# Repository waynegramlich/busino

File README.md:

# Busino

The Busino is an "Arduino-compatible" processor board.

Since just about everybody calls their board "Arduino-compatible",
even when they are not really very compatible, it is prudent to
be more specific.  The Busino uses an Atmel<Sup>&tm;</Sup> AVR
ATmega324P processor.  This processor is in a 40-pin DIP (Dual
In-line Package) and is pretty compatible with the ATmega328
that is used by the ever popular Arudino<Sup>&tm;</Sup> Uno
processor board.  The ATmega324P is used instead of the AtMega324
because it has a second UART (Universal Asynchronous
Receiver/Transmitter) that is reserved for bus communication
between multiple Busino's.  The processor runs at 16MHz just
like the Uno.  The Busino has the same connectors as the Uno
so that most of the Arduino Uno compatible shield can be plugged
into the Busino.  The Busino can be programmed using the
Arduino IDE (Integrated Development Environment.)  Since the
ATmega324P has different package pin assignments, a Busino template
needs to be installed with the IDE to make it work.  Lastly, the
Busino uses a USB to serial cable to program the board instead
of having a dedicated USB to serial conversion chip.  In short,
the Busino is **extremely** compatible with the
Arduino<Sup>&tm;</Sup> system architecture.

There are three other major features of the Busino:

1 There is 10-pin ribbon cable connector that can be used to
  bus multiple Busino's together.  The Busino uses CAN bus
  physical layer transceivers (technically ISO-11898 transceivers)
  over a differential pair for communication.  This is exactly
  the same technology used by automobile manufacturers.  It is
  extremely robust.

  This bus has two power buses -- one for supplying power to
  digital logic (e.g. microprocessors, etc.) and another for
  supplying power to small motors like hobby servos, etc.  The
  separate power buses, reduce noise and cross talk issues.

2 The Busino also has 4 locations to plug in Mini-Shields.
  A mini-shield is very similar in concept to an Arduino
  shield, only smaller.  A mini-shield is 5cm &times; 5cm
  square and has access to all of the power (5V, 3V, Vin)
  and signal pins (D0-D13, A0-A5, RESET, etc.) that are
  accessible to an Arduino shield.  Since there are 4 mini-shield
  locations, up to 4 mini-shields can be plugged into the
  Busino.

3 The Busino is 100% Open Source Hardware and Software.
  The PCB's (Printed Circuit Boards) are designed using
  KiCAD (an open source PCB layout tool.)   The Software
  is released under a GPL software license.  You can 
  make any modifications you want, provided that you
  adhere the very reasonable license requirements.  In
  short, since the Busino team is sharing the stuff with
  you, we want you to share your awesome modifications
  back with us.  If you can make money selling Busino's,
  it is your money, not ours.

## Schematic

The schematic and PCB were developed using the KiCAD
EDA (Engineering Design Automation) software suite.
Like the Busino, KiCAD is also 100% open source with
no arbitrary restrictions.

The schematic described below is for the revision B
of the board.  Each revision is kept in a separate
directory.  Revision B is kept in the `rev_b` directory.
The schematic can be found in `busino.pdf` in the `rev_b`
directory.

The schematic is broken into 7 sheets:

* The top level sheet just shows the common bus that connects
  together all of the common "Arduino" pins between all the
  sheets.  These include D0-D13, A0-A5, #RESET, AREF, and various
  power lines -- VIN, 5V, 3V3, GND, MPWR, and MGND.

* The processor sheet contains most of the *meat* in that
  it shows how the processor is wired up to everything --
  the bus, the voltage regulators, the reset circuitry,
  etc.

* The Arduino shield sheet shows how all of the pins are
  connected to the standard pins that connect to Arudino
  compatible shields.

* The remaining 4 sheets are essentially duplicates of one
  another, where each sheet documents the two connectors
  that connect to a mini-shield.

### Processor Schematic Sheet

Logic power comes in via VIN and is run through
a 5V LDO (Low Drop-Out) LM2940 voltage regulator (U1)
and through another 3.3V LDO LM117T-3.3 volttage
regulator (U3).  It is recommended that at least 6V
be provided to VIN.  C1, C3, and C5 are 22uF tantalum
capacitors to help with regulation.  The .1uF 
capacitor (C8) and .47 Ohm series connection reduces
the ESR (Equivalent Series Resistance) of C3 down
to between 1 and .1 Ohms.  This is required to ensure
that the LM2940 voltage regulator remains stable.
The LM2940 specification sheet can be found in the
`docs` directory.  The 3.3V power output is not
used by the processor; it is only there to provide
3.3V to any Arduino compatible shields that get plugged
into the Busino.   U3 and C5 can be omitted if 3.3V
is not required.

The bus is comes in via 2x5 shrouded header (N8).
MPWR and MGND are directed to the mini-shields to
provide power for motors and such.  LGND and LPWR
supply the logic power.  LPWR is also called VIN
because that is what the Arduino folks called it.

The bus signals come in on CANH and CANL which are
a differential pair that adhere to ISO-11898.  The are
fed into a Microchip MCP2562 CAN bus transceiver (U2).
The TXD and RXD signals are fed to RXD1 and TXD1 on
the processor (U5).  The termination jumper (J1) can
be configured to supply 120 Ohms of termination if
the Busino is at either end of the bus.

The processor is an ATmega324P and comes in 40-pin
DIP (Dual In-line Package).  The goal is to make
the ATmega324P be as compatible as possible with
the standard ATmega328 that is used by the Arduino Uno
product.  Since the ATmega328 comes in a 28-pin DIP
there are some differences in the pin assignments.
These have been carefully thought out.  PB1 and PD4
are connected because the Arduino has both a PWM
output and T1 attached to the same line.  PD4 has
a PWM output and PB1 has T1.  Along similar lines,
PD7 is connected to PB5, PC0 is connected to PA5,
and PC1 is connected to PA4.  The standard Arduino
16MHz crystal (X1) and two 18pF capacitors (C2 and C4)
connected to XTAL1 and XTAL2.

Since it was basically free to do so, an AVR compatible
2x5 shrouded header (N16) is provided for JTAG debugging.
It is expected that only people who really want to do
this, will need the JTAG connector, so they will have
to find the connector and solder it in.

The processor is programmed to have a bootloader installed
in it.  Unlike the Arduino, the Busino does not have a
dedicated USB to serial connection.  Instead it uses
a common USB to serial connector from FTDI.  The FTDI
cable can be either a 5V cable or a 3.3V cable.  In
general the 3.3V cable is preferred.  The FTDI cable
plugs into the 1x6 header (N9).  The RXD and TXD
signals are routed through 1K resistors (R2 and R3) to
the RXD0 and TXD0 pins of the processor (U5).  The 1K
resistor allows an Arduino shield to *override* the
programming that comes in the FTDI cable.

It should be noted that the output of TXD from the processor
is 5V.  The 3.3V FTDI serial cable has 5V tolerant inputs
so no damage occurs.  Also, the TXD output from the FTDI
cable is either 3.3V or 5V.  For the processor #RESET line,
any voltage above .6*Vcc (= .6*5V = .3V) is treated as a
"high".  Both 3.3V and 5V are within specification.

The processor can be reset in any of the following
methods:

* The reset button (SW1) can be depressed.

* The JTAG adapter (N16) can assert #NRST

* The bus can send a "break" character which will cause the
  processor to reset.

* The host computer can assert #RTS on the FTD cable (N9).

The #RTS signal can be either 3.3V or 5V.  This is fed
into U4F which is a 74HCT05 open collector inverter.
The HCT logic family will treat any voltage that exceeds
2V as a logic "high".  The 100K pull-up resistor R4
ensures that the U4F input is pulled high if no FTDI
serial cable is plugged in.  U4F and U4E basically
provide a buffer that converts any 3.3V signals up to 5V.
The 100K resistor R12 is needed because U4F has an open
collector output.

The two 10K resistors (R7, R13) in conjunction with .1uF
capacitor (C6) and Schottky diode (D1) used to generate
a #RESET pulse as follows:

* The #RTS line idles "high".  This cause both ends of C6
  to be pulled up to 5V, thereby fully discharging C6 so
  that there is 0V across it.

* At the beginning of programming, #RTS is asserted low by
  the programming software for the duration of programming.
  When #RTS is asserted low, the output of U4E goes low.
  Since there is 0V across C6, the #RESET line is pulled
  low as well.  This causes the processor (U5) to be reset.

* Immediately after U4E goes low, starts charging up to 5V
  through the 10K resistor (R7).  Eventually, the voltage
  on the #RESET line charges up high enough for the processor
  to decide that the #RESET condition is no longer present
  and it starts executing instructions.

* At the end of programming, #RTS goes high again.  There is
  now 5V across C6.  When #RTS goes high, the output of U4E
  is pulled high to 5V and 5V across C6 causes the voltage
  on the #RESET line to head towards 10V (5V + 5V = 10V.)
  While the processor #RESET input can tolerate up to 13V,
  the JTAG #NRST driver may not be as forgiving.  Hence,
  Schottky diode D1 is used to clamp the voltage on #RESET
  to no higher than 5.2V.  (A Schottky diode does not drop
  more than .2V.)

The bus reset circuitry is not as complicated.

* The 100K resistor (R11) pulls up the input to U4A to ensure
  that that no spurious reset occurs if the MCP2562 chip is
   not plugged in.

* Since the TXD output idles "high", the output of U4A idles
  "low".  When U4A is "low", it forms a voltage divider from
  5V with a 10K resistor and 180 Ohm resistor.  This produces
  a voltage of .09V across .1uF capacitor C7.  This is a "low"
  voltage which is inverted to a "high" through open collector
  inverter U4B.  The 10K resistor R7 pulls #RESET high.

* To trigger a reset, the bus master send a "break" signal down
  the line.  This causes TXD from the CAN bus transceiver (U2)
  to go low, and causes .1uF capacitor (C7) to "slowly" charge
  towards 5V.  Eventually, the voltage across C7 exceed 2V
  and causes U4B to invert the "high" signal on its open
  collector output.  This asserts #RESET low and resets the
  processor.

* When the bus master release the reset line by setting the
  bus back to idle.  This causes the U4A output to go low
  again, which discharges the .1uF capacitor (C7) through
  the 180 Ohm resistor (R5).  C7 discharges back down to .09V.
  This cause the output of open collector inverter U4B to be
  pulled back up to 5V by 10K resistor R7 and forces #RESET
  back "high" again.  This causes the processor (U5) to start
  executing instructions.

The reason why the standard bus data transfers do not trigger
a reset is because the worst case data transfer has 1 lower
start bit, followed by 9 data zeros, followed by 1 high stop
bit.  Thus, in worst case the data bus is low 10/11 of the
time.  The resistor values of R5 and R6 are chosen to ensure
that the 1 high stop bit will discharge capacitor C7 faster than
the 10 low bits can cause C7 to charge.

### Arduino Shield Schematic Sheet

{More here.}

### Mini-Shield Schematic Sheets

{More here.}

## Rev. B

### Issues

* The C1 "+" silk is next to C8.  It belongs next to R8.
  C3 and C1 have "opposite" polarity. [x]

* C6 and C7 should be 1uF in schematic? [C6 yes, C7 no]

* Artwork for R4 is covered by U5 socket. [x]

* R10 artwork overlaps with D2 artrwork. [x]

* Tie unused inputs of inverter to 0V/5V. [x]

* Switch from using 74HCT05 to using 74HCT03 for availability
  reasons. [x]

* The TXD and RXD lines on the CAN bus transceiver are swapped. [x]

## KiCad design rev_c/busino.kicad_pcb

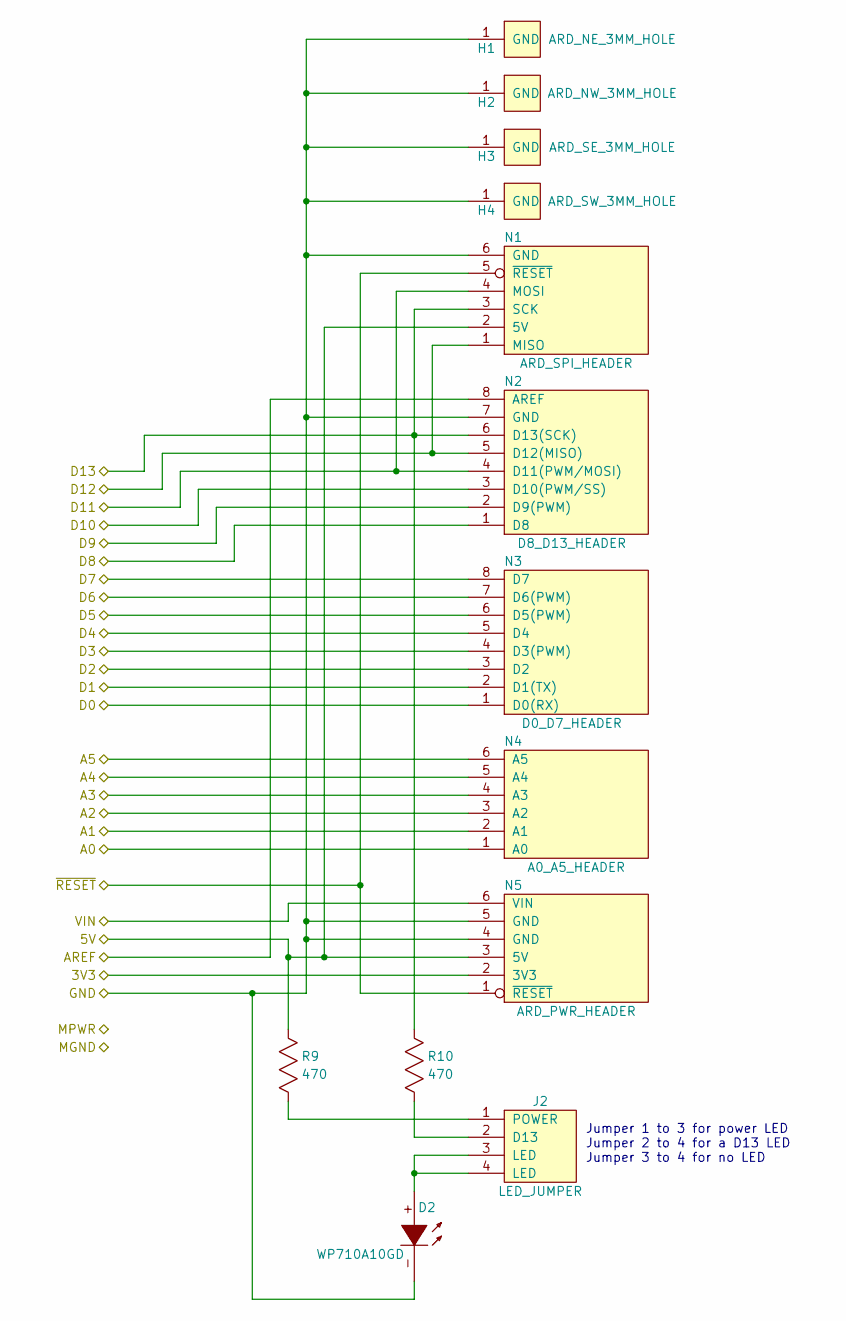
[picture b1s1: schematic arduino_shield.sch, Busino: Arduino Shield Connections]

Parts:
D2: WP710A10GD; T1_LED
H1: ARD_NE_3MM_HOLE; MountingHole_3mm
H2: ARD_NW_3MM_HOLE; MountingHole_3mm
H3: ARD_SE_3MM_HOLE; MountingHole_3mm
H4: ARD_SW_3MM_HOLE; MountingHole_3mm
J2: LED_JUMPER; Pin_Header_Straight_2x02
N1: ARD_SPI_HEADER; Pin_Header_Straight_2x03
N2: D8_D13_HEADER; Pin_Header_Straight_1x08
N3: D0_D7_HEADER; Pin_Header_Straight_1x08
N4: A0_A5_HEADER; Pin_Header_Straight_1x06
N5: ARD_PWR_HEADER; Pin_Header_Straight_1x06
R9, R10: 470; Resistor_Horizontal__400

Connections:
+3.3V: N5.2 (3V3); also elsewhere on the board
+5V: N1.2 (5V), N5.3 (5V), R9.2; also elsewhere on the board
/Arduino Shield/A0: N4.1 (A0); also elsewhere on the board
/Arduino Shield/A1: N4.2 (A1); also elsewhere on the board
/Arduino Shield/A2: N4.3 (A2); also elsewhere on the board
/Arduino Shield/A3: N4.4 (A3); also elsewhere on the board
/Arduino Shield/A4: N4.5 (A4); also elsewhere on the board
/Arduino Shield/A5: N4.6 (A5); also elsewhere on the board
/Arduino Shield/AREF: N2.8 (AREF); also elsewhere on the board
/Arduino Shield/D0: N3.1 (D0(RX)); also elsewhere on the board
/Arduino Shield/D1: N3.2 (D1(TX)); also elsewhere on the board
/Arduino Shield/D2: N3.3 (D2); also elsewhere on the board
/Arduino Shield/D3: N3.4 (D3(PWM)); also elsewhere on the board
/Arduino Shield/D4: N3.5 (D4); also elsewhere on the board
/Arduino Shield/D5: N3.6 (D5(PWM)); also elsewhere on the board
/Arduino Shield/D6: N3.7 (D6(PWM)); also elsewhere on the board
/Arduino Shield/D7: N3.8 (D7); also elsewhere on the board
/Arduino Shield/D8: N2.1 (D8); also elsewhere on the board
/Arduino Shield/D9: N2.2 (D9(PWM)); also elsewhere on the board
/Arduino Shield/D10: N2.3 (D10(PWM/SS)); also elsewhere on the board
/Arduino Shield/D11: N1.4 (MOSI), N2.4 (D11(PWM/MOSI)); also elsewhere on the board
/Arduino Shield/D12: N1.1 (MISO), N2.5 (D12(MISO)); also elsewhere on the board
/Arduino Shield/D13: N1.3 (SCK), N2.6 (D13(SCK)), R10.2; also elsewhere on the board
/Arduino Shield/VIN: N5.6 (VIN); also elsewhere on the board
/Arduino Shield/~RESET: N1.5 (~RESET), N5.1 (~RESET); also elsewhere on the board
GND: D2.-, H1.1, H2.1, H3.1, H4.1, N1.6 (GND), N2.7 (GND), N5.4 (GND), N5.5 (GND); also elsewhere on the board
unnamed: D2.+, J2.3 (LED), J2.4 (LED)
unnamed: J2.1 (POWER), R9.1
unnamed: J2.2 (D13), R10.1

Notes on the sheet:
Jumper 1 to 3 for power LED Jumper 2 to 4 for a D13 LED Jumper 3 to 4 for no LED

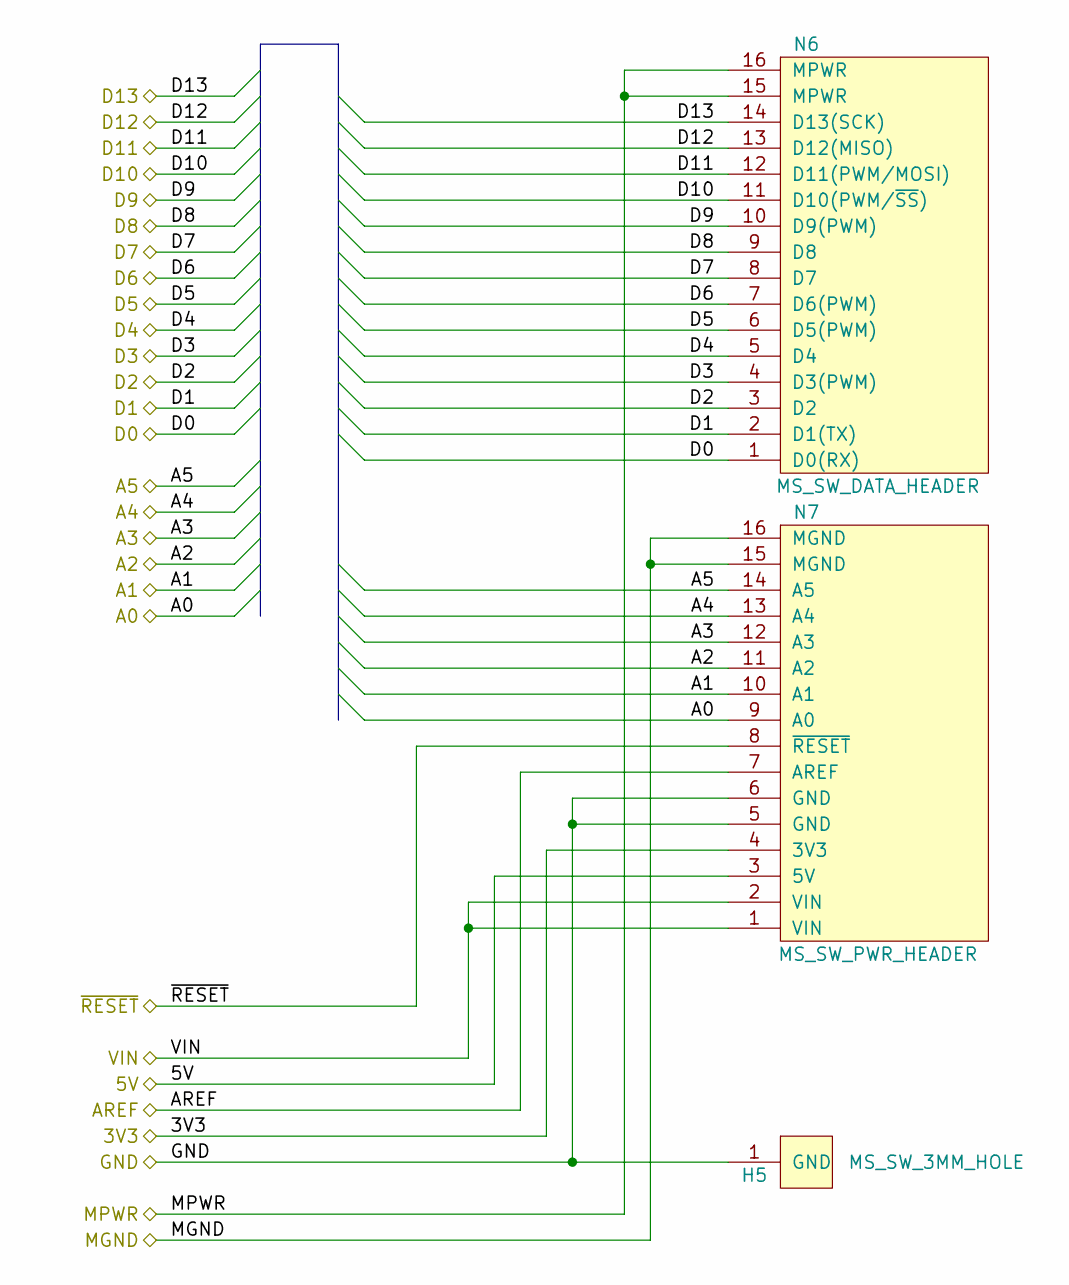
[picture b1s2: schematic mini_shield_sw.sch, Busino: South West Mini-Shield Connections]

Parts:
H5: MS_SW_3MM_HOLE; MountingHole_3mm
N6: MS_SW_DATA_HEADER; Pin_Header_Straight_2x08
N7: MS_SW_PWR_HEADER; Pin_Header_Straight_2x08

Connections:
+3.3V: N7.4 (3V3); also elsewhere on the board
+5V: N7.3 (5V); also elsewhere on the board
/Arduino Shield/A0: N7.9 (A0); also elsewhere on the board
/Arduino Shield/A1: N7.10 (A1); also elsewhere on the board
/Arduino Shield/A2: N7.11 (A2); also elsewhere on the board
/Arduino Shield/A3: N7.12 (A3); also elsewhere on the board
/Arduino Shield/A4: N7.13 (A4); also elsewhere on the board
/Arduino Shield/A5: N7.14 (A5); also elsewhere on the board
/Arduino Shield/AREF: N7.7 (AREF); also elsewhere on the board
/Arduino Shield/D0: N6.1 (D0(RX)); also elsewhere on the board
/Arduino Shield/D1: N6.2 (D1(TX)); also elsewhere on the board
/Arduino Shield/D2: N6.3 (D2); also elsewhere on the board
/Arduino Shield/D3: N6.4 (D3(PWM)); also elsewhere on the board
/Arduino Shield/D4: N6.5 (D4); also elsewhere on the board
/Arduino Shield/D5: N6.6 (D5(PWM)); also elsewhere on the board
/Arduino Shield/D6: N6.7 (D6(PWM)); also elsewhere on the board
/Arduino Shield/D7: N6.8 (D7); also elsewhere on the board
/Arduino Shield/D8: N6.9 (D8); also elsewhere on the board
/Arduino Shield/D9: N6.10 (D9(PWM)); also elsewhere on the board
/Arduino Shield/D10: N6.11 (D10(PWM/~SS)); also elsewhere on the board
/Arduino Shield/D11: N6.12 (D11(PWM/MOSI)); also elsewhere on the board
/Arduino Shield/D12: N6.13 (D12(MISO)); also elsewhere on the board
/Arduino Shield/D13: N6.14 (D13(SCK)); also elsewhere on the board
/Arduino Shield/MGND: N7.15 (MGND), N7.16 (MGND); also elsewhere on the board
/Arduino Shield/MPWR: N6.15 (MPWR), N6.16 (MPWR); also elsewhere on the board
/Arduino Shield/VIN: N7.1 (VIN), N7.2 (VIN); also elsewhere on the board
/Arduino Shield/~RESET: N7.8 (~RESET); also elsewhere on the board
GND: H5.1, N7.5 (GND), N7.6 (GND); also elsewhere on the board

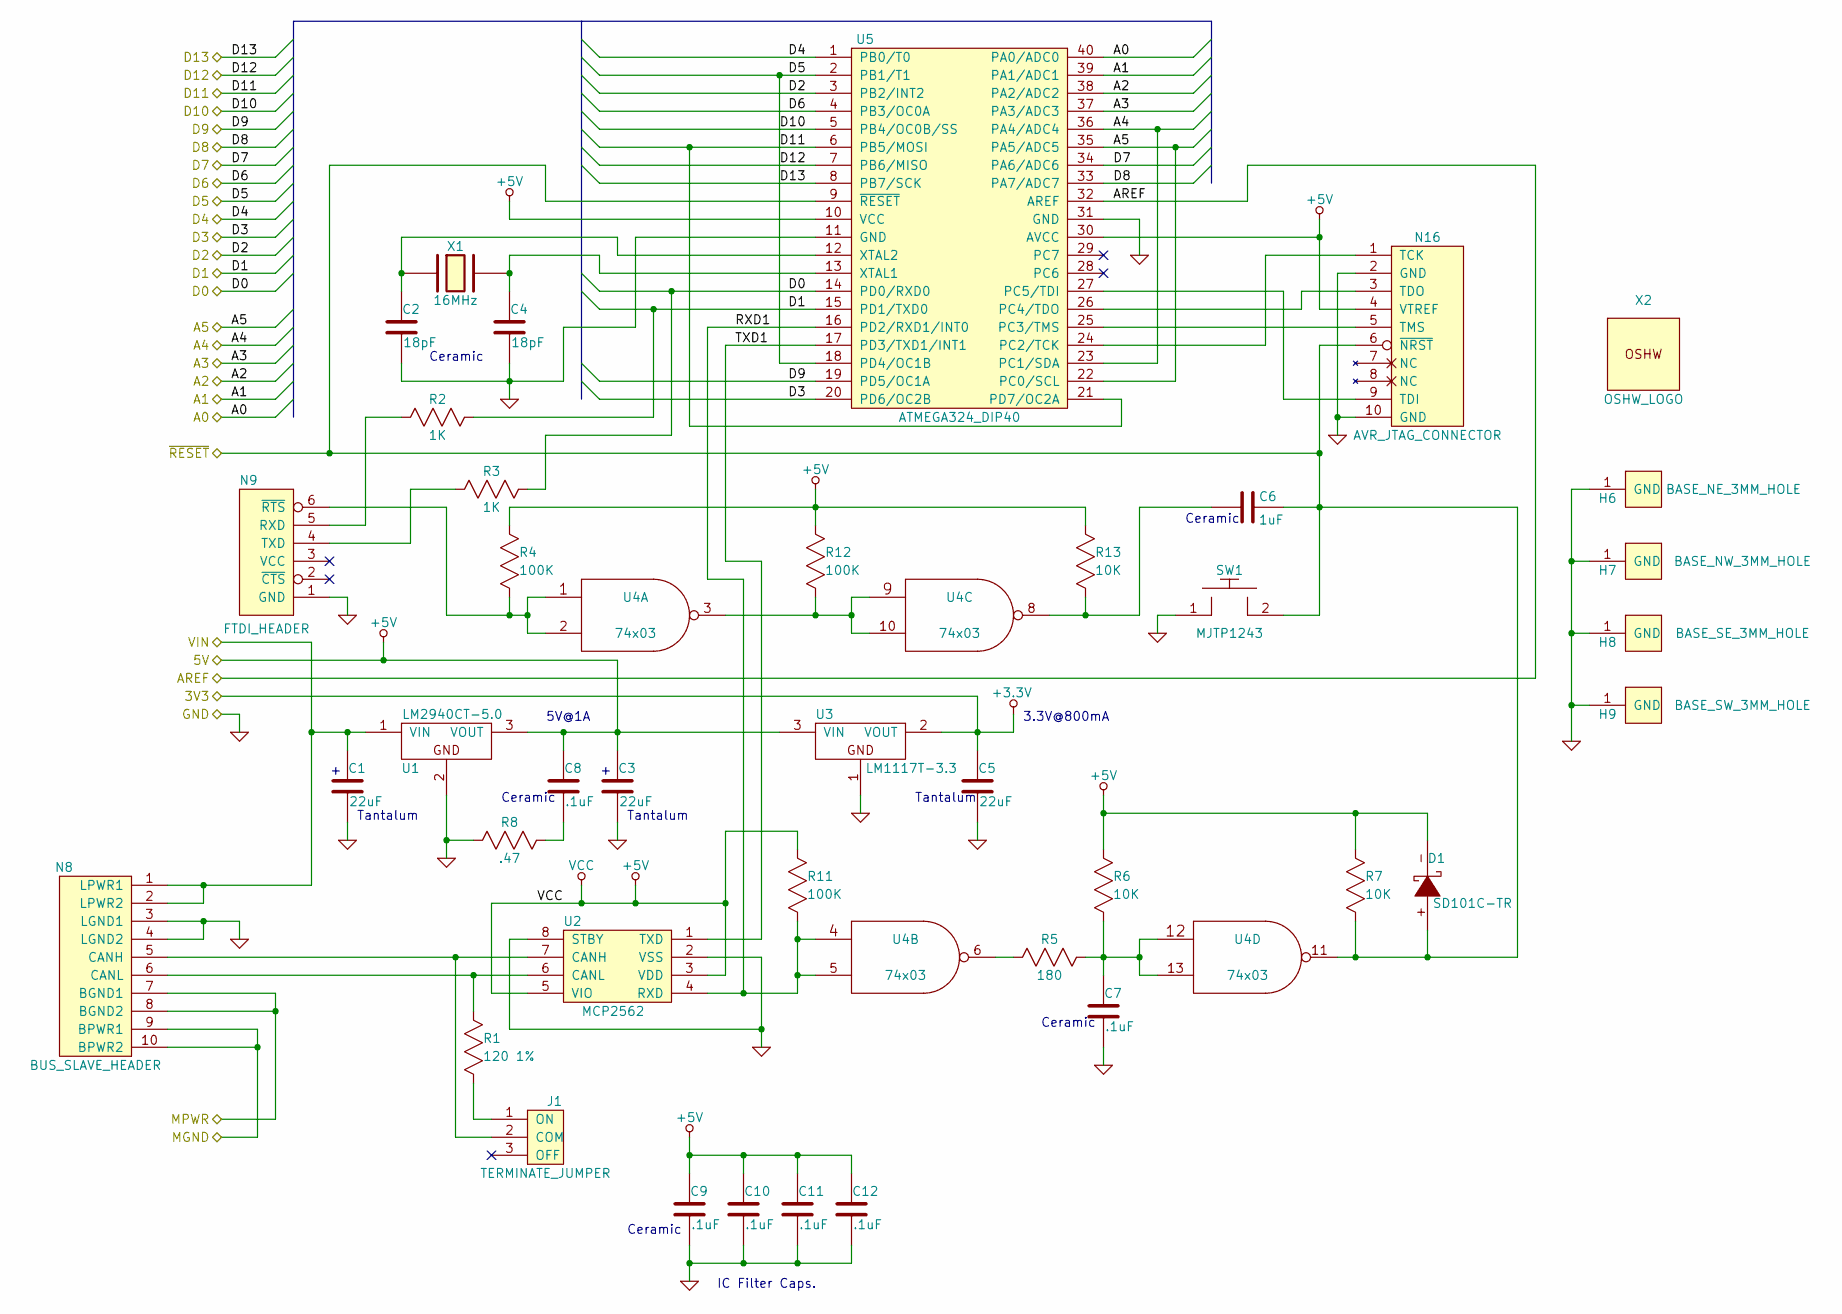
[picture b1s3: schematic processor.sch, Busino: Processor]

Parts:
C1, C3, C5: 22uF; Capacitor3MMDiscRM2.5
C2, C4: 18pF; Capacitor3MMDiscRM2.5
C6: 1uF; Capacitor3MMDiscRM2.5
C7, C8, C9, C10, C11, C12: .1uF; Capacitor3MMDiscRM2.5
D1: SD101C-TR; Diode_DO-41_SOD81_Horizontal_RM10
H6: BASE_NE_3MM_HOLE; MountingHole_3mm
H7: BASE_NW_3MM_HOLE; MountingHole_3mm
H8: BASE_SE_3MM_HOLE; MountingHole_3mm
H9: BASE_SW_3MM_HOLE; MountingHole_3mm
J1: TERMINATE_JUMPER; Pin_Header_Straight_1x03
N8: BUS_SLAVE_HEADER; Pin_Header_Straight_2x05_Shrouded
N9: FTDI_HEADER; Pin_Header_Straight_1x06
N16: AVR_JTAG_CONNECTOR; Pin_Header_Straight_2x05_Shrouded
R1: 120 1%; Resistor_Horizontal__400
R2, R3: 1K; Resistor_Horizontal__400
R4, R11, R12: 100K; Resistor_Horizontal__400
R5: 180; Resistor_Horizontal__400
R6, R7, R13: 10K; Resistor_Horizontal__400
R8: .47; Resistor_Horizontal__400
SW1: MJTP1243; BUTTON_6.5MM
U1: LM2940CT-5.0; Regulator_TO_220_Horizontal
U2: MCP2562; DIP-8__300
U3: LM1117T-3.3; Regulator_TO_220_Horizontal
U4: 74x03; DIP-14__300
U5: ATMEGA324_DIP40; DIP-40__600
X1: 16MHz; Crystal_HC49-U_Vertical
X2: OSHW_LOGO; OSHW_LOGO_250mil

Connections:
+3.3V: C5.1, U3.2 (VOUT); also elsewhere on the board
+5V: C3.1, C8.1, C9.1, C10.1, C11.1, C12.1, D1.-, N16.4 (VTREF), R4.2, R6.2, R7.2, R11.2, R12.2, R13.2, U1.3 (VOUT), U2.3 (VDD), U2.5 (VIO), U3.3 (VIN), U4.14 (VCC), U5.10 (VCC), U5.30 (AVCC); also elsewhere on the board
/Arduino Shield/A0: U5.40 (PA0/ADC0); also elsewhere on the board
/Arduino Shield/A1: U5.39 (PA1/ADC1); also elsewhere on the board
/Arduino Shield/A2: U5.38 (PA2/ADC2); also elsewhere on the board
/Arduino Shield/A3: U5.37 (PA3/ADC3); also elsewhere on the board
/Arduino Shield/A4: U5.23 (PC1/SDA), U5.36 (PA4/ADC4); also elsewhere on the board
/Arduino Shield/A5: U5.22 (PC0/SCL), U5.35 (PA5/ADC5); also elsewhere on the board
/Arduino Shield/AREF: U5.32 (AREF); also elsewhere on the board
/Arduino Shield/D0: R3.2, U5.14 (PD0/RXD0); also elsewhere on the board
/Arduino Shield/D1: R2.2, U5.15 (PD1/TXD0); also elsewhere on the board
/Arduino Shield/D2: U5.3 (PB2/INT2); also elsewhere on the board
/Arduino Shield/D3: U5.20 (PD6/OC2B); also elsewhere on the board
/Arduino Shield/D4: U5.1 (PB0/T0); also elsewhere on the board
/Arduino Shield/D5: U5.2 (PB1/T1), U5.18 (PD4/OC1B); also elsewhere on the board
/Arduino Shield/D6: U5.4 (PB3/OC0A); also elsewhere on the board
/Arduino Shield/D7: U5.34 (PA6/ADC6); also elsewhere on the board
/Arduino Shield/D8: U5.33 (PA7/ADC7); also elsewhere on the board
/Arduino Shield/D9: U5.19 (PD5/OC1A); also elsewhere on the board
/Arduino Shield/D10: U5.5 (PB4/OC0B/SS); also elsewhere on the board
/Arduino Shield/D11: U5.6 (PB5/MOSI), U5.21 (PD7/OC2A); also elsewhere on the board
/Arduino Shield/D12: U5.7 (PB6/MISO); also elsewhere on the board
/Arduino Shield/D13: U5.8 (PB7/SCK); also elsewhere on the board
/Arduino Shield/MGND: N8.9 (BPWR1), N8.10 (BPWR2); also elsewhere on the board
/Arduino Shield/MPWR: N8.7 (BGND1), N8.8 (BGND2); also elsewhere on the board
/Arduino Shield/VIN: C1.1, N8.1 (LPWR1), N8.2 (LPWR2), U1.1 (VIN); also elsewhere on the board
/Arduino Shield/~RESET: C6.2, D1.+, N16.6 (~NRST), R7.1, SW1.2, U4.11, U5.9 (~RESET); also elsewhere on the board
/Processor/RXD1: R11.1, U2.4 (RXD), U4.4, U4.5, U5.16 (PD2/RXD1/INT0)
/Processor/TXD1: U2.1 (TXD), U5.17 (PD3/TXD1/INT1)
GND: C1.2, C2.2, C3.2, C4.2, C5.2, C7.2, C9.2, C10.2, C11.2, C12.2, H6.1, H7.1, H8.1, H9.1, N8.3 (LGND1), N8.4 (LGND2), N9.1 (GND), N16.2 (GND), N16.10 (GND), R8.1, SW1.1, U1.2, U2.2 (VSS), U2.8 (STBY), U3.1, U4.7 (GND), U5.11 (GND), U5.31 (GND); also elsewhere on the board
unnamed: C2.1, U5.12 (XTAL2), X1.1
unnamed: C4.1, U5.13 (XTAL1), X1.2
unnamed: C6.1, R13.1, U4.8
unnamed: C7.1, R5.2, R6.1, U4.12, U4.13
unnamed: C8.2, R8.2
unnamed: J1.1 (ON), R1.1
unnamed: J1.2 (COM), N8.5 (CANH), U2.7 (CANH)
unnamed: N8.6 (CANL), R1.2, U2.6 (CANL)
unnamed: N9.4 (TXD), R3.1
unnamed: N9.5 (RXD), R2.1
unnamed: N9.6 (~RTS), R4.1, U4.1, U4.2
unnamed: N16.1 (TCK), U5.24 (PC2/TCK)
unnamed: N16.3 (TDO), U5.26 (PC4/TDO)
unnamed: N16.5 (TMS), U5.25 (PC3/TMS)
unnamed: N16.9 (TDI), U5.27 (PC5/TDI)
unnamed: R5.1, U4.6
unnamed: R12.1, U4.3, U4.9, U4.10

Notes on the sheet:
Ceramic
Tantalum
5V@1A
3.3V@800mA
IC Filter Caps.

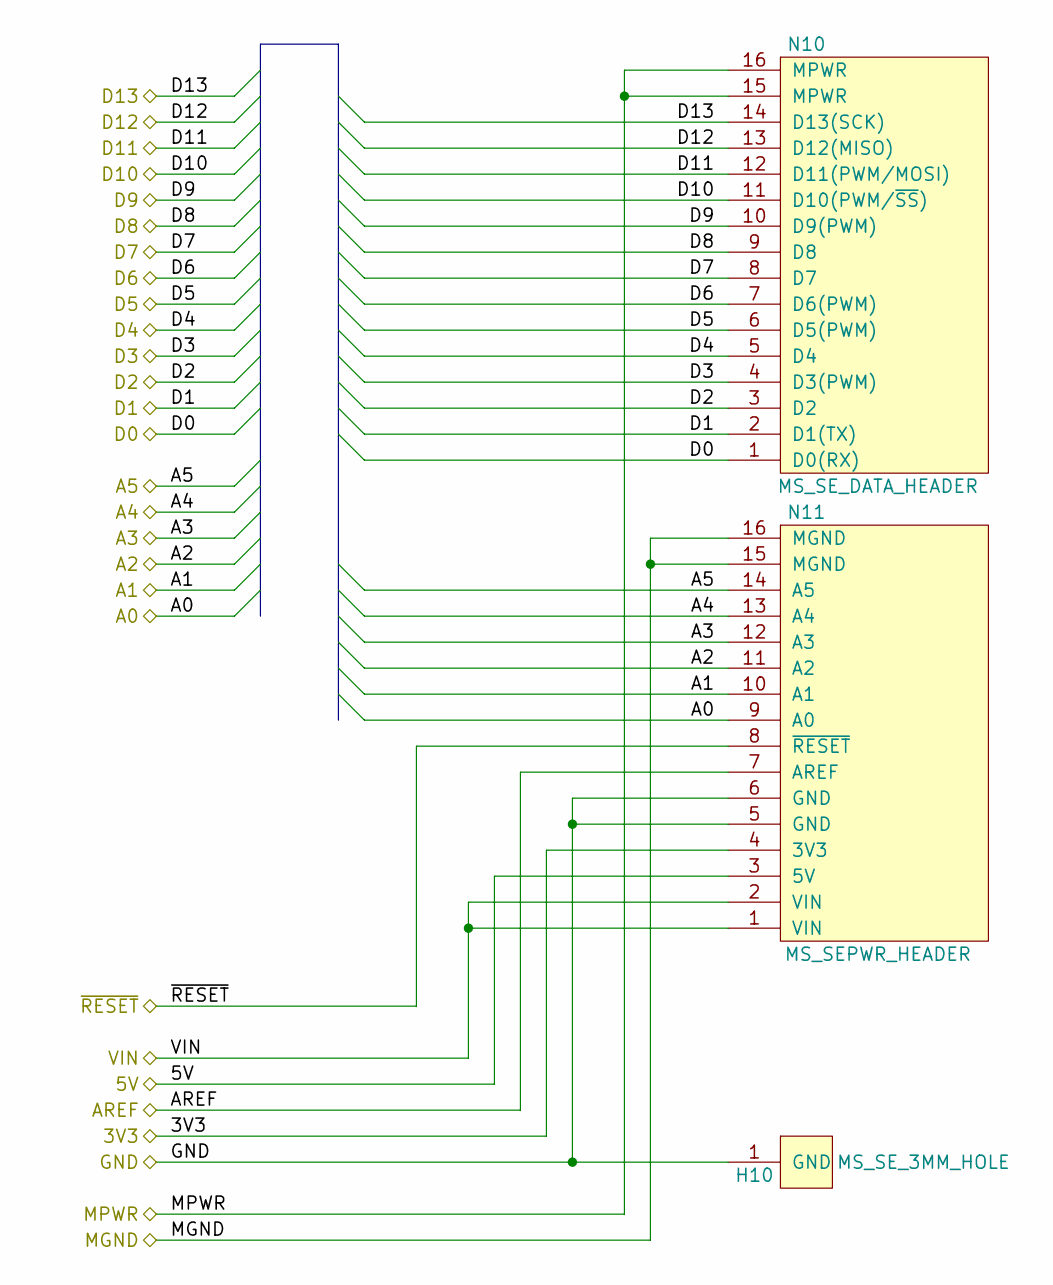
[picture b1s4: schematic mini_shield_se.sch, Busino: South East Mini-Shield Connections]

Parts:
H10: MS_SE_3MM_HOLE; MountingHole_3mm
N10: MS_SE_DATA_HEADER; Pin_Header_Straight_2x08
N11: MS_SEPWR_HEADER; Pin_Header_Straight_2x08

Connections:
+3.3V: N11.4 (3V3); also elsewhere on the board
+5V: N11.3 (5V); also elsewhere on the board
/Arduino Shield/A0: N11.9 (A0); also elsewhere on the board
/Arduino Shield/A1: N11.10 (A1); also elsewhere on the board
/Arduino Shield/A2: N11.11 (A2); also elsewhere on the board
/Arduino Shield/A3: N11.12 (A3); also elsewhere on the board
/Arduino Shield/A4: N11.13 (A4); also elsewhere on the board
/Arduino Shield/A5: N11.14 (A5); also elsewhere on the board
/Arduino Shield/AREF: N11.7 (AREF); also elsewhere on the board
/Arduino Shield/D0: N10.1 (D0(RX)); also elsewhere on the board
/Arduino Shield/D1: N10.2 (D1(TX)); also elsewhere on the board
/Arduino Shield/D2: N10.3 (D2); also elsewhere on the board
/Arduino Shield/D3: N10.4 (D3(PWM)); also elsewhere on the board
/Arduino Shield/D4: N10.5 (D4); also elsewhere on the board
/Arduino Shield/D5: N10.6 (D5(PWM)); also elsewhere on the board
/Arduino Shield/D6: N10.7 (D6(PWM)); also elsewhere on the board
/Arduino Shield/D7: N10.8 (D7); also elsewhere on the board
/Arduino Shield/D8: N10.9 (D8); also elsewhere on the board
/Arduino Shield/D9: N10.10 (D9(PWM)); also elsewhere on the board
/Arduino Shield/D10: N10.11 (D10(PWM/~SS)); also elsewhere on the board
/Arduino Shield/D11: N10.12 (D11(PWM/MOSI)); also elsewhere on the board
/Arduino Shield/D12: N10.13 (D12(MISO)); also elsewhere on the board
/Arduino Shield/D13: N10.14 (D13(SCK)); also elsewhere on the board
/Arduino Shield/MGND: N11.15 (MGND), N11.16 (MGND); also elsewhere on the board
/Arduino Shield/MPWR: N10.15 (MPWR), N10.16 (MPWR); also elsewhere on the board
/Arduino Shield/VIN: N11.1 (VIN), N11.2 (VIN); also elsewhere on the board
/Arduino Shield/~RESET: N11.8 (~RESET); also elsewhere on the board
GND: H10.1, N11.5 (GND), N11.6 (GND); also elsewhere on the board

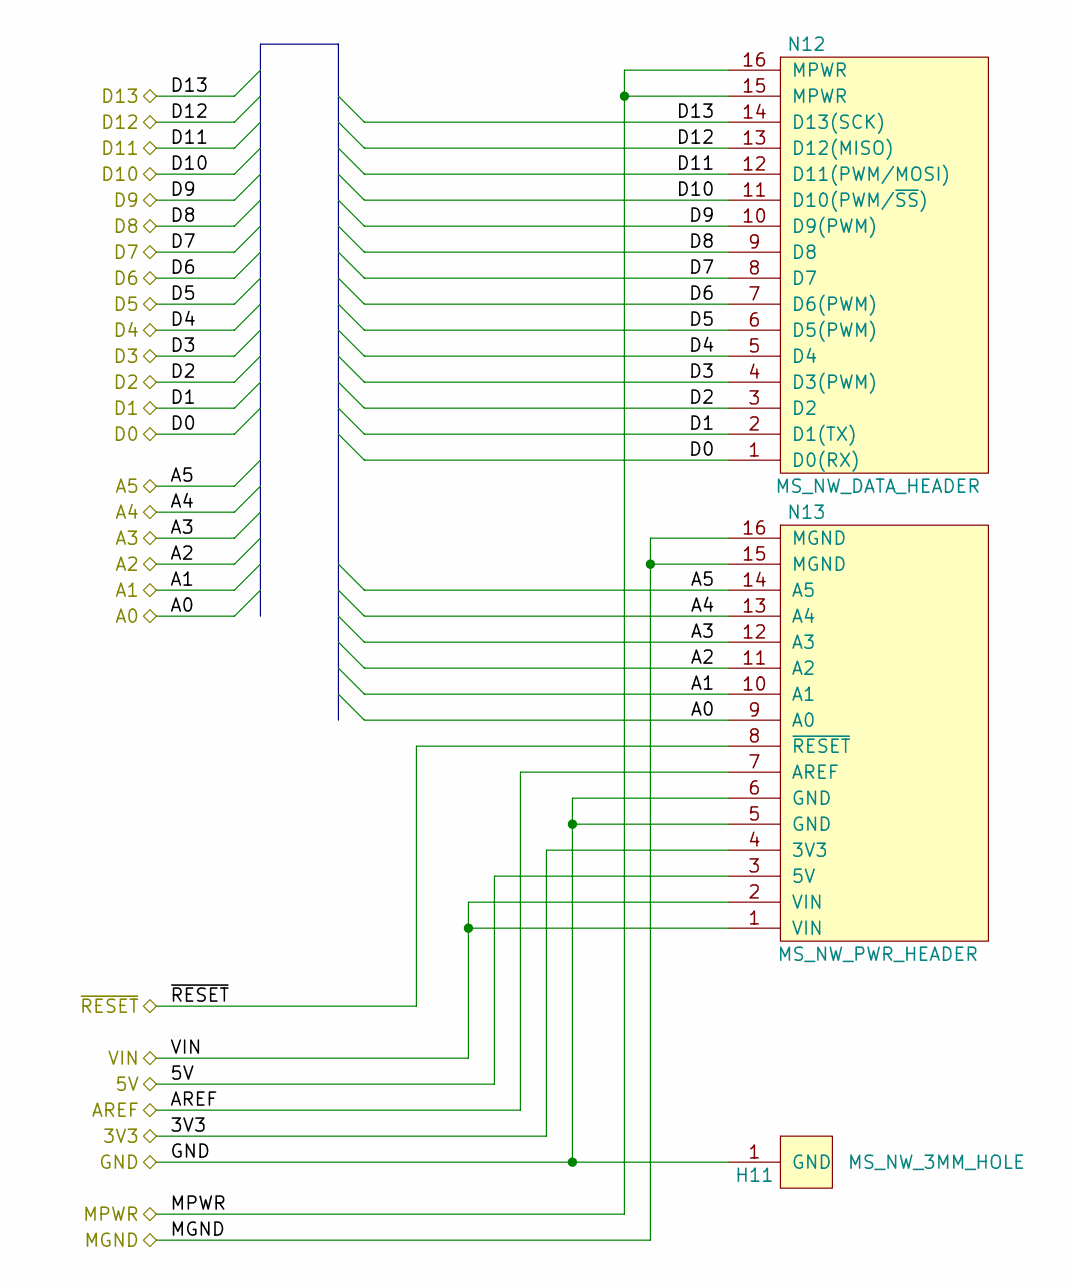
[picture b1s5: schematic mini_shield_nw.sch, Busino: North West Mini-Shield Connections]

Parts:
H11: MS_NW_3MM_HOLE; MountingHole_3mm
N12: MS_NW_DATA_HEADER; Pin_Header_Straight_2x08
N13: MS_NW_PWR_HEADER; Pin_Header_Straight_2x08

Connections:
+3.3V: N13.4 (3V3); also elsewhere on the board
+5V: N13.3 (5V); also elsewhere on the board
/Arduino Shield/A0: N13.9 (A0); also elsewhere on the board
/Arduino Shield/A1: N13.10 (A1); also elsewhere on the board
/Arduino Shield/A2: N13.11 (A2); also elsewhere on the board
/Arduino Shield/A3: N13.12 (A3); also elsewhere on the board
/Arduino Shield/A4: N13.13 (A4); also elsewhere on the board
/Arduino Shield/A5: N13.14 (A5); also elsewhere on the board
/Arduino Shield/AREF: N13.7 (AREF); also elsewhere on the board
/Arduino Shield/D0: N12.1 (D0(RX)); also elsewhere on the board
/Arduino Shield/D1: N12.2 (D1(TX)); also elsewhere on the board
/Arduino Shield/D2: N12.3 (D2); also elsewhere on the board
/Arduino Shield/D3: N12.4 (D3(PWM)); also elsewhere on the board
/Arduino Shield/D4: N12.5 (D4); also elsewhere on the board
/Arduino Shield/D5: N12.6 (D5(PWM)); also elsewhere on the board
/Arduino Shield/D6: N12.7 (D6(PWM)); also elsewhere on the board
/Arduino Shield/D7: N12.8 (D7); also elsewhere on the board
/Arduino Shield/D8: N12.9 (D8); also elsewhere on the board
/Arduino Shield/D9: N12.10 (D9(PWM)); also elsewhere on the board
/Arduino Shield/D10: N12.11 (D10(PWM/~SS)); also elsewhere on the board
/Arduino Shield/D11: N12.12 (D11(PWM/MOSI)); also elsewhere on the board
/Arduino Shield/D12: N12.13 (D12(MISO)); also elsewhere on the board
/Arduino Shield/D13: N12.14 (D13(SCK)); also elsewhere on the board
/Arduino Shield/MGND: N13.15 (MGND), N13.16 (MGND); also elsewhere on the board
/Arduino Shield/MPWR: N12.15 (MPWR), N12.16 (MPWR); also elsewhere on the board
/Arduino Shield/VIN: N13.1 (VIN), N13.2 (VIN); also elsewhere on the board
/Arduino Shield/~RESET: N13.8 (~RESET); also elsewhere on the board
GND: H11.1, N13.5 (GND), N13.6 (GND); also elsewhere on the board

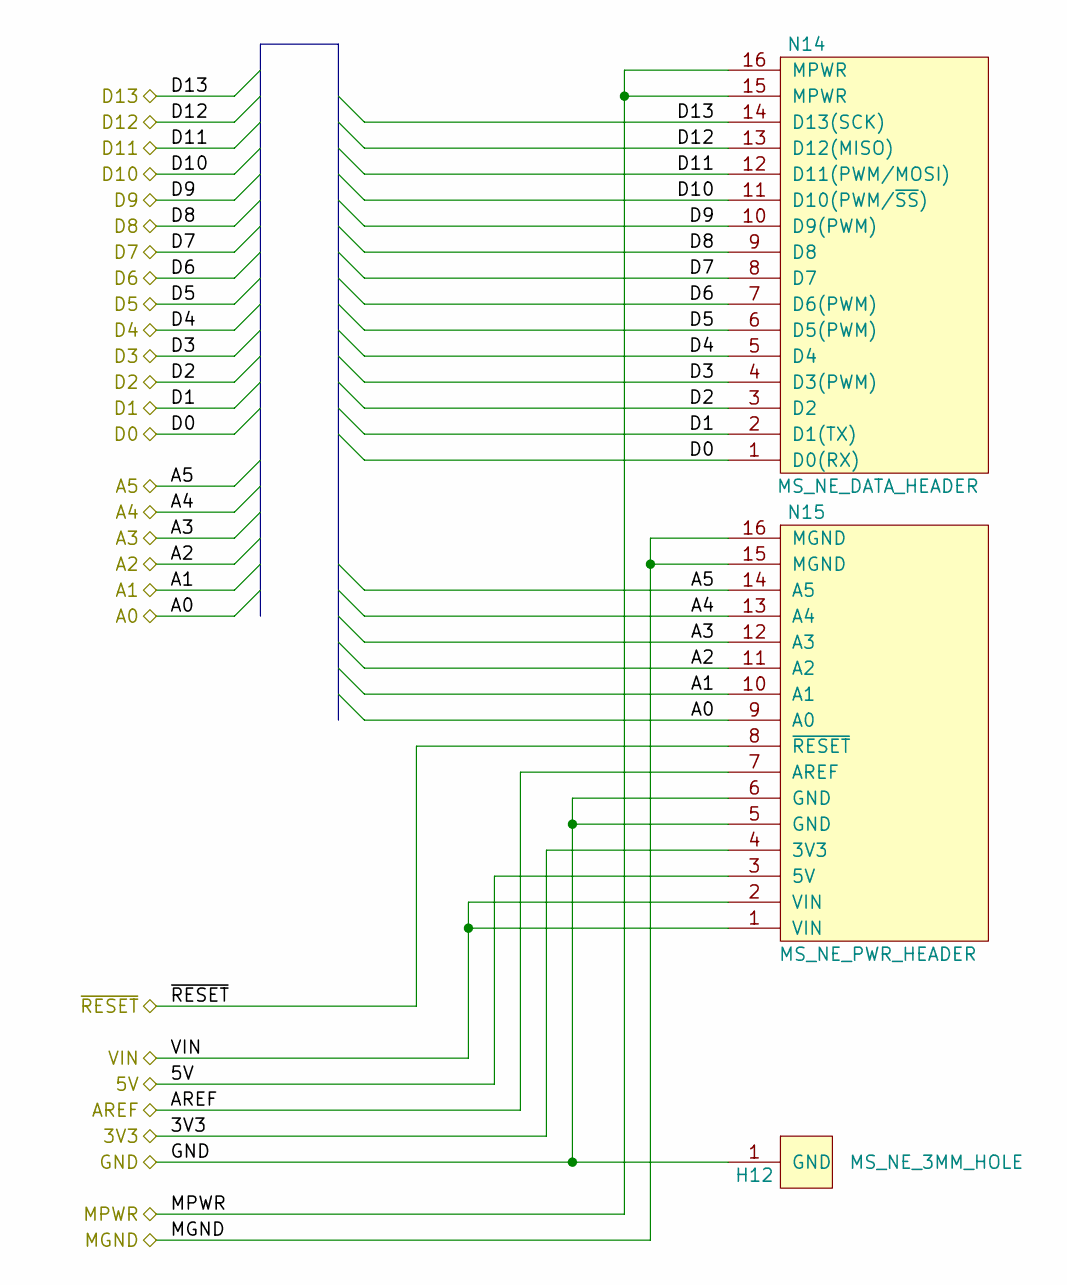
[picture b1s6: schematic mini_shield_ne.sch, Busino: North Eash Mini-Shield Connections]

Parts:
H12: MS_NE_3MM_HOLE; MountingHole_3mm
N14: MS_NE_DATA_HEADER; Pin_Header_Straight_2x08
N15: MS_NE_PWR_HEADER; Pin_Header_Straight_2x08

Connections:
+3.3V: N15.4 (3V3); also elsewhere on the board
+5V: N15.3 (5V); also elsewhere on the board
/Arduino Shield/A0: N15.9 (A0); also elsewhere on the board
/Arduino Shield/A1: N15.10 (A1); also elsewhere on the board
/Arduino Shield/A2: N15.11 (A2); also elsewhere on the board
/Arduino Shield/A3: N15.12 (A3); also elsewhere on the board
/Arduino Shield/A4: N15.13 (A4); also elsewhere on the board
/Arduino Shield/A5: N15.14 (A5); also elsewhere on the board
/Arduino Shield/AREF: N15.7 (AREF); also elsewhere on the board
/Arduino Shield/D0: N14.1 (D0(RX)); also elsewhere on the board
/Arduino Shield/D1: N14.2 (D1(TX)); also elsewhere on the board
/Arduino Shield/D2: N14.3 (D2); also elsewhere on the board
/Arduino Shield/D3: N14.4 (D3(PWM)); also elsewhere on the board
/Arduino Shield/D4: N14.5 (D4); also elsewhere on the board
/Arduino Shield/D5: N14.6 (D5(PWM)); also elsewhere on the board
/Arduino Shield/D6: N14.7 (D6(PWM)); also elsewhere on the board
/Arduino Shield/D7: N14.8 (D7); also elsewhere on the board
/Arduino Shield/D8: N14.9 (D8); also elsewhere on the board
/Arduino Shield/D9: N14.10 (D9(PWM)); also elsewhere on the board
/Arduino Shield/D10: N14.11 (D10(PWM/~SS)); also elsewhere on the board
/Arduino Shield/D11: N14.12 (D11(PWM/MOSI)); also elsewhere on the board
/Arduino Shield/D12: N14.13 (D12(MISO)); also elsewhere on the board
/Arduino Shield/D13: N14.14 (D13(SCK)); also elsewhere on the board
/Arduino Shield/MGND: N15.15 (MGND), N15.16 (MGND); also elsewhere on the board
/Arduino Shield/MPWR: N14.15 (MPWR), N14.16 (MPWR); also elsewhere on the board
/Arduino Shield/VIN: N15.1 (VIN), N15.2 (VIN); also elsewhere on the board
/Arduino Shield/~RESET: N15.8 (~RESET); also elsewhere on the board
GND: H12.1, N15.5 (GND), N15.6 (GND); also elsewhere on the board

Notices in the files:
rev_c/busino.kicad_pcb:
Copyright (c) 2014
